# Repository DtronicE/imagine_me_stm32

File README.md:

# STM32 Custom Development Board

A first custom STM32 development-board project, designed to explore the full hardware workflow—from schematic capture and PCB layout in KiCad to configuring the STM32F103C8T6 in STM32CubeMX.

This repository includes the board’s design files and project configuration. The design brings together USB device support, USART1, I2C2, and SWD programming/debugging in a compact 2-layer board. It is a learning-focused project, and the files are shared as a basis for continued review and refinement.

## Hardware Features
- STM32F103C8T6 microcontroller
- 3.3V regulated power supply for the MCU and peripherals
- SWD programming and debugging header
- USB device interface for serial communication and debugging
- USART1 support for UART communication
- I2C2 support for peripheral connectivity
- Solid ground plane for improved signal integrity
- 2-layer FR4 PCB implementation
- Custom symbol and footprint work in the KiCad project

## Technical Highlights
- Core microcontroller: STM32F103C8T6-based design
- Power system: 3.3V regulation for the MCU and supporting circuitry
- Debugging interface: SWD port for flashing and debugging
- Communication interfaces: USB device support, I2C2, and USART1
- PCB implementation: 2-layer FR4 layout with a solid ground plane
- Library work: manually verified footprint and symbol data against datasheet references when applicable

## Design Specifications
- Layer count: 2-layer FR4 board
- Grounding strategy: continuous ground plane used on both layers to improve signal integrity and reduce noise
- Routing: signal paths kept short and organized for a clean, manageable first-pass PCB layout
- DRC status: design checks completed successfully with no electrical errors reported in the project workflow

## Project Contents
- `stm32.kicad_sch` — schematic
- `stm32.kicad_pcb` — PCB layout
- `design1.ioc` — STM32CubeMX project configuration
- `New_Library_0.kicad_sym` — custom symbol library
- `README.md` — project overview and notes

## Notes
This project represents a learning-focused board design and is intended as a practical embedded hardware exercise. Improvements and revisions can be made as the design evolves.

## Status
The repository currently contains the KiCad source files and the associated project configuration needed to continue refining the board design.

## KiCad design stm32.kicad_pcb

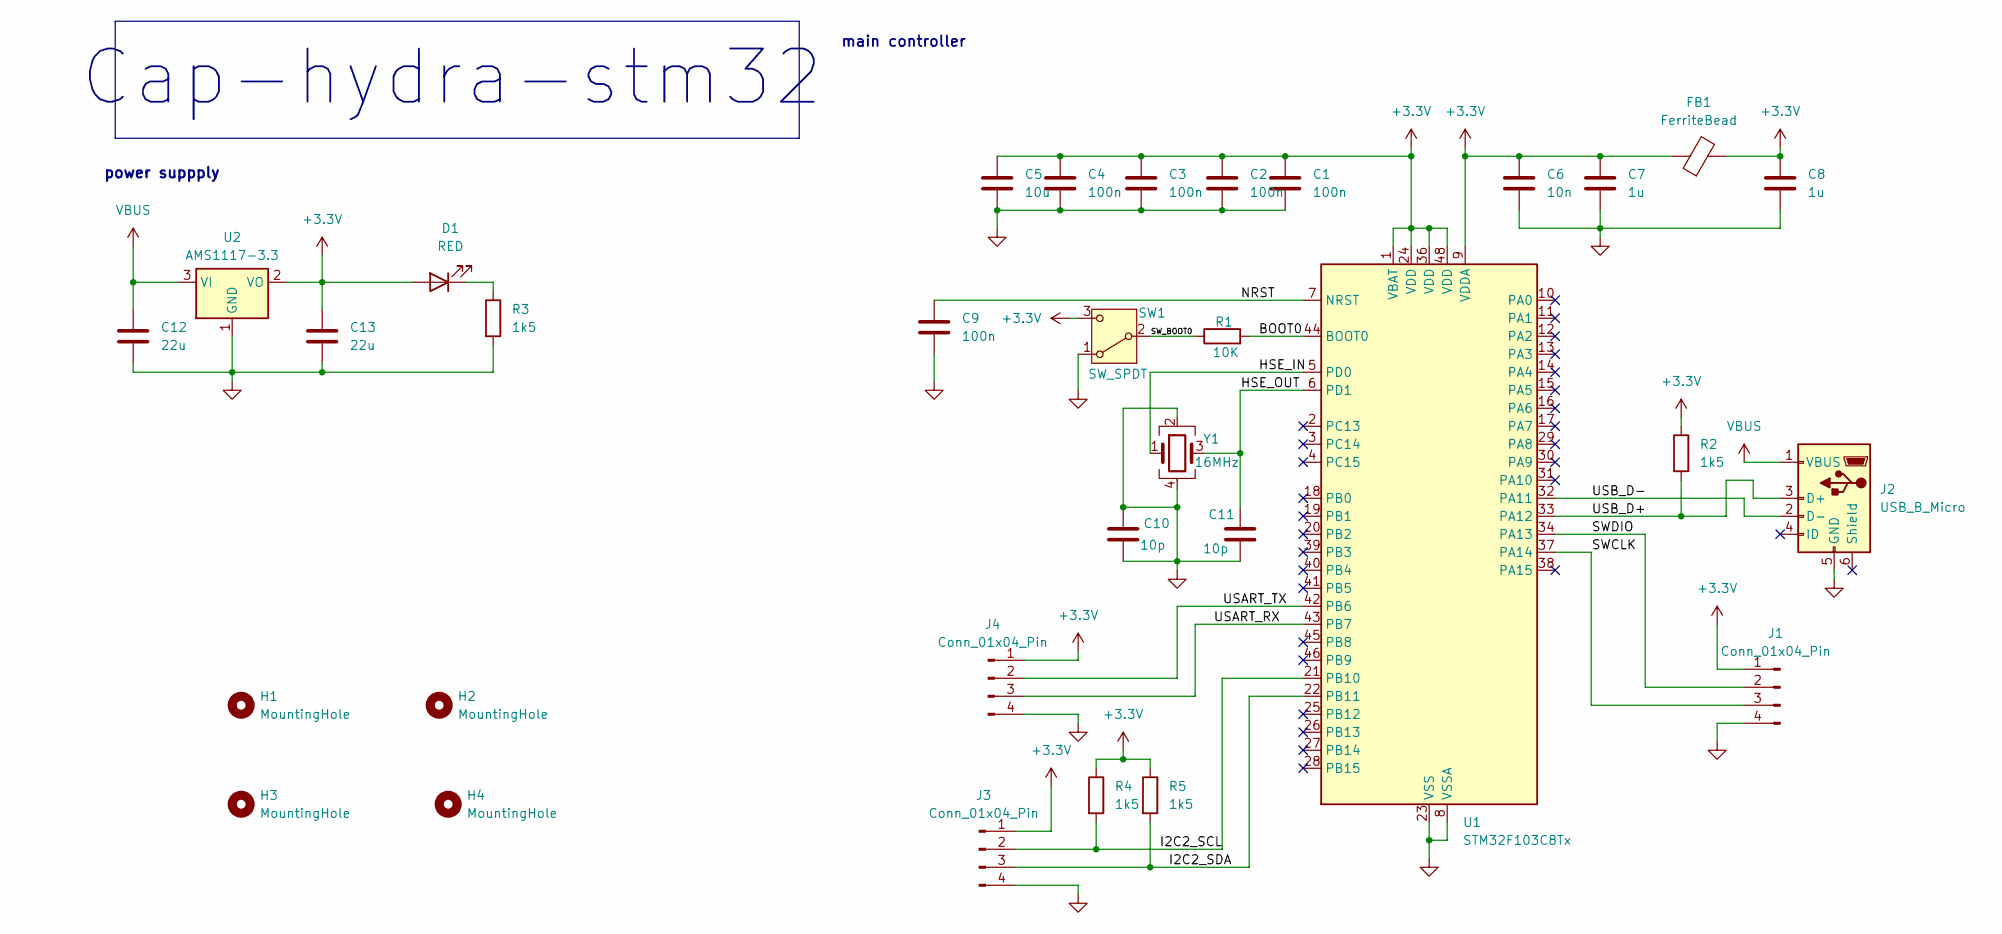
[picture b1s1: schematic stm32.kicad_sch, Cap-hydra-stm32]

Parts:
C1, C2, C3, C4, C9: 100n; C_01005_0402Metric
C5: 10u; C_01005_0402Metric
C6: 10n; C_01005_0402Metric
C7, C8: 1u; C_01005_0402Metric
C10, C11: 10p; C_01005_0402Metric
C12, C13: 22u; C_01005_0402Metric
D1: RED; LED_0603_1608Metric
FB1: FerriteBead; L_0201_0603Metric
H1, H2, H3, H4: MountingHole; MountingHole_2.1mm
J1, J3, J4: Conn_01x04_Pin; PinHeader_1x04_P2.54mm_Vertical
J2: USB_B_Micro; USB_Micro-B_Wuerth_629105150521
R1: 10K; R_01005_0402Metric
R2, R3, R4, R5: 1k5; R_01005_0402Metric
SW1: SW_SPDT; SW_SPST_B3U-1100P
U1: STM32F103C8Tx; LQFP-48_7x7mm_P0.5mm
U2: AMS1117-3.3; SOT-223-3_TabPin2
Y1: 16MHz; Crystal_SMD_3225-4Pin_3.2x2.5mm

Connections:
+3.3V: C1.1, C2.1, C3.1, C4.1, C5.1, C6.1, C7.1, C8.1, C13.1, D1.2 (A), FB1.1, FB1.2, J1.1, J3.1, J4.1, R2.1, R4.1, R5.1, SW1.3 (C), U1.1 (VBAT), U1.9 (VDDA), U1.24 (VDD), U1.36 (VDD), U1.48 (VDD), U2.2 (VO)
/BOOT0: R1.2, U1.44 (BOOT0)
/HSE_IN: U1.5 (PD0), Y1.1
/HSE_OUT: C11.1, U1.6 (PD1), Y1.3
/I2C2_SCL: J3.2, R4.2, U1.21 (PB10)
/I2C2_SDA: J3.3, R5.2, U1.22 (PB11)
/NRST: C9.1, U1.7 (NRST)
/SWCLK: J1.3, U1.37 (PA14)
/SWDIO: J1.2, U1.34 (PA13)
/SW_BOOT0: R1.1, SW1.2 (B)
/USART_RX: J4.3, U1.43 (PB7)
/USART_TX: J4.2, U1.42 (PB6)
/USB_D+: J2.3 (D+), R2.2, U1.33 (PA12)
/USB_D-: J2.2 (D-), U1.32 (PA11)
GND: C1.2, C2.2, C3.2, C4.2, C5.2, C6.2, C7.2, C8.2, C9.2, C10.1, C10.2, C11.2, C12.2, C13.2, J1.4, J2.5 (GND), J3.4, J4.4, R3.2, SW1.1 (A), U1.8 (VSSA), U1.23 (VSS), U1.35 (VSS), U1.47 (VSS), U2.1 (GND), Y1.2 (G), Y1.4
unnamed: D1.1 (K), R3.1
VBUS: C12.1, J2.1 (VBUS), U2.3 (VI)

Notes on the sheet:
Cap-hydra-stm32
main controller
power suppply

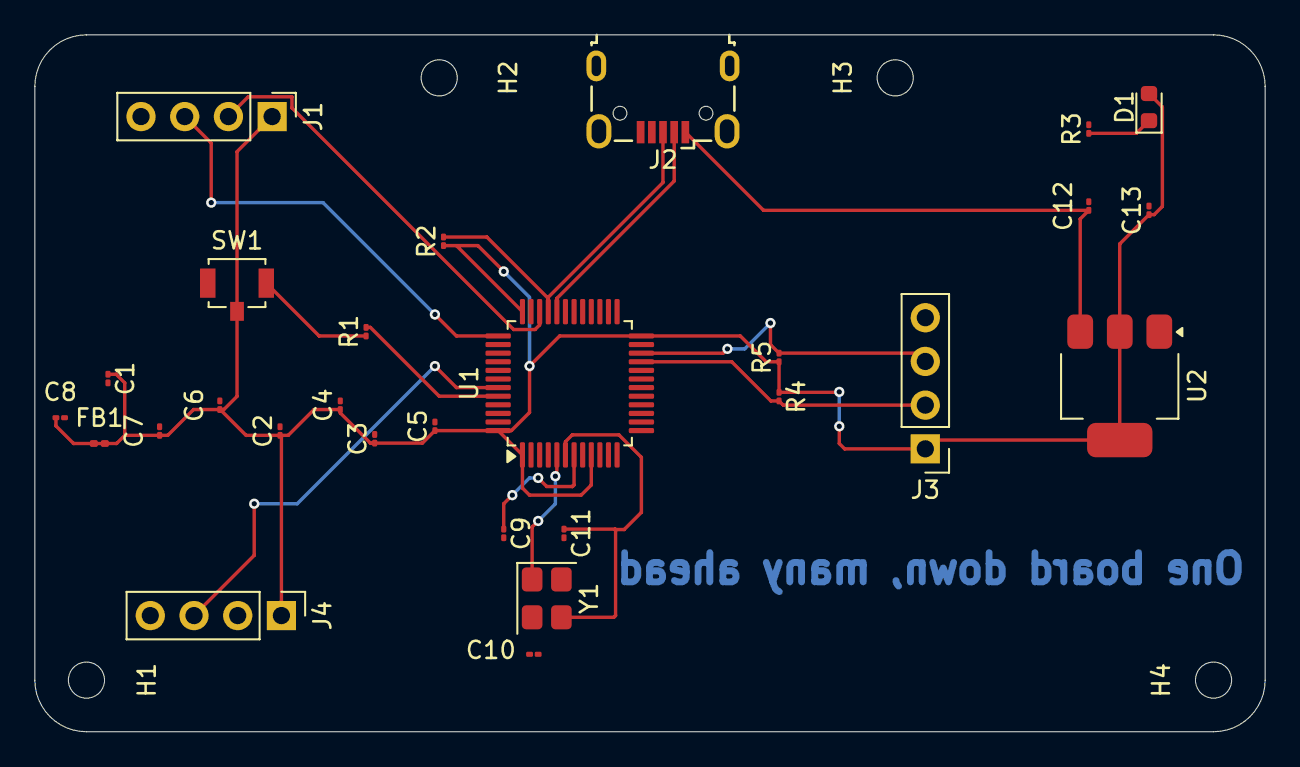
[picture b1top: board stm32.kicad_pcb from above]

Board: 2 copper layers, 71.5 x 40.5 mm, 32 parts (0 on the bottom side), 17 nets.

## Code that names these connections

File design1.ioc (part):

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Mcu.Name=STM32F103C(8-B)Tx
Mcu.Package=LQFP48
Mcu.UserName=STM32F103C8Tx
PA11.Mode=Device
PA11.Signal=USB_DM
PA12.Mode=Device
PA12.Signal=USB_DP
PA13.Mode=Serial_Wire
PA13.Signal=SYS_JTMS-SWDIO
PA14.Mode=Serial_Wire
PA14.Signal=SYS_JTCK-SWCLK
PB10.Mode=I2C
PB10.Signal=I2C2_SCL
PB11.Mode=I2C
PB11.Signal=I2C2_SDA
PB6.Mode=Asynchronous
PB6.Signal=USART1_TX
PB7.Mode=Asynchronous
PB7.Signal=USART1_RX
PD0-OSC_IN.Mode=HSE-External-Oscillator
PD0-OSC_IN.Signal=RCC_OSC_IN
PD1-OSC_OUT.Mode=HSE-External-Oscillator
PD1-OSC_OUT.Signal=RCC_OSC_OUT
RCC.SYSCLKFreq_VALUE=48000000
RCC.SYSCLKSource=RCC_SYSCLKSOURCE_PLLCLK
board=custom

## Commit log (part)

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2026-01-13 Add README for STM32 development board project
    Added a detailed README for the STM32 project, outlining the project overview, technical highlights, design specifications, and DRC status.
2026-01-13 Revise README to emphasize STM32 project overview
    Removed introductory text and focused on the project overview.
